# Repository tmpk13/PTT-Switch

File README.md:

# ptt-switch

A push-to-talk switch: a wire on the board is a capacitive touch electrode,
and a WCH CH572D (RISC-V, BLE 5) senses it and reports over Bluetooth Low
Energy. KiCad 10 project in `ptt-switch/`, powered by a 3.6 V Li-SOCl2
cell and flashed through an SWD header with a WCH-LinkE;
`enclosure/` builds a parametric FreeCAD box for it from
`enclosure/params.toml`. `firmware/` is the CH572D's Rust firmware: it
sleeps between touch polls and reports the wire's state to a phone app
as described in [docs/BLE.md](docs/BLE.md). `android/` is that app: for
now it finds a board, connects and shows whether the wire is touched.

| Task | Command |
|------|---------|
| Tests: CH572D pinout, netlist against the intended circuit, enclosure geometry, firmware logic, app protocol | `mise run test` |
| Firmware: build, then flash through a WCH-LinkE on J4 (within 5 s of power-up) | `mise run fw:flash` |
| Firmware: build only | `mise run fw:build` |
| ERC (report in `build/erc.rpt`) | `mise run erc` |
| Enclosure: FCStd, STEP and STL per part into `enclosure/build/` | `mise run box:build` |
| Enclosure: build, then open in the FreeCAD GUI | `mise run box:open` |
| App: build, install on the phone attached over adb, start | `mise run app:install` |

FreeCAD is not installed by mise; see
[NOTES.md](NOTES.md#freecad-location) where it is not on PATH.

Design decisions and their reasons: [NOTES.md](NOTES.md). Block diagram and
the touch measurement sequence: [ARCHITECTURE.md](ARCHITECTURE.md).

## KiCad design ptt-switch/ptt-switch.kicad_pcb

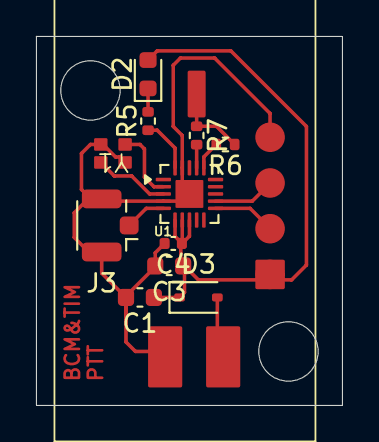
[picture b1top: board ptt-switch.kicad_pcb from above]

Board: 2 copper layers, 17.0 x 20.5 mm, 11 parts (0 on the bottom side), 10 nets.

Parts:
C1: 100u; C_0603_1608Metric
C3: 2.2u; C_0603_1608Metric
C4: 100n; C_0402_1005Metric
D2: LED; LED_0603_1608Metric
D3: BAT54WS; D_SOD-323
J3: U.FL; U.FL_Hirose_U.FL-R-SMT-1_Vertical
R5: 1k; R_0402_1005Metric
R6: 10k; R_0402_1005Metric
R7: 1M; R_0402_1005Metric
U1: CH572D
Y1: 32MHz; XRCGB32M000F1S1DR0

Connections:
+3V3: C1.1, C3.1, C4.1, D2.2 (A), D3.1 (K), U1.6 (VDD33), U1.7 (VIO33), U1.8 (V5)
/ANT: J3.1 (In), U1.5 (ANT)
/TOUCH: R6.1, R7.1
GND: C1.2, C3.2, C4.2, J3.2 (Ext), U1.4 (NC), U1.19 (NC), U1.21 (GND), Y1.2
unnamed: D2.1 (K), R5.2
unnamed: R5.1, U1.20 (PA2)
unnamed: R6.2, U1.16 (PA7)
unnamed: R7.2, U1.17 (PA10)
unnamed: U1.3 (XI), Y1.3
unnamed: U1.2 (XO), Y1.1
